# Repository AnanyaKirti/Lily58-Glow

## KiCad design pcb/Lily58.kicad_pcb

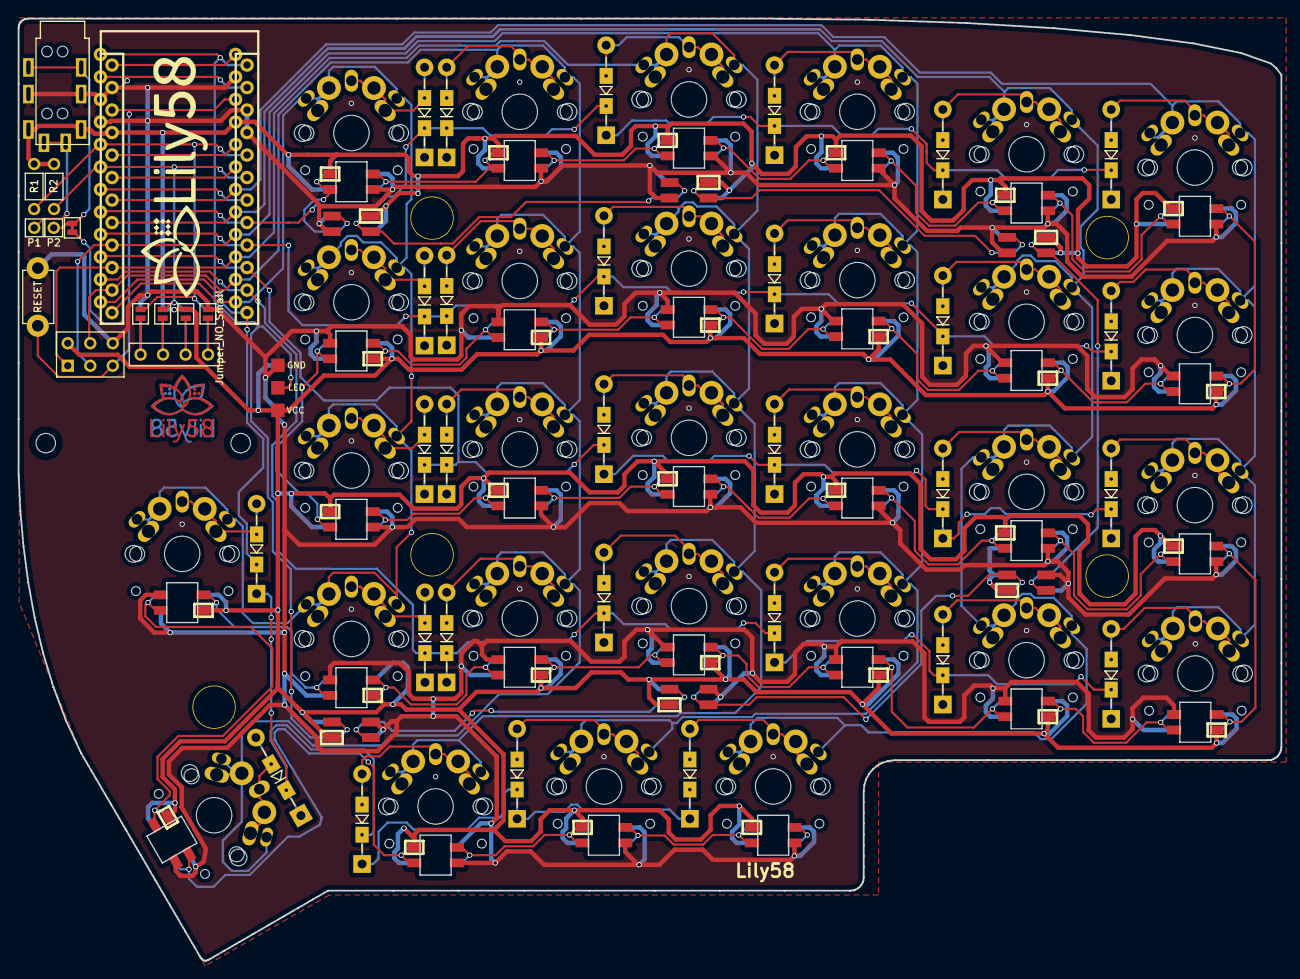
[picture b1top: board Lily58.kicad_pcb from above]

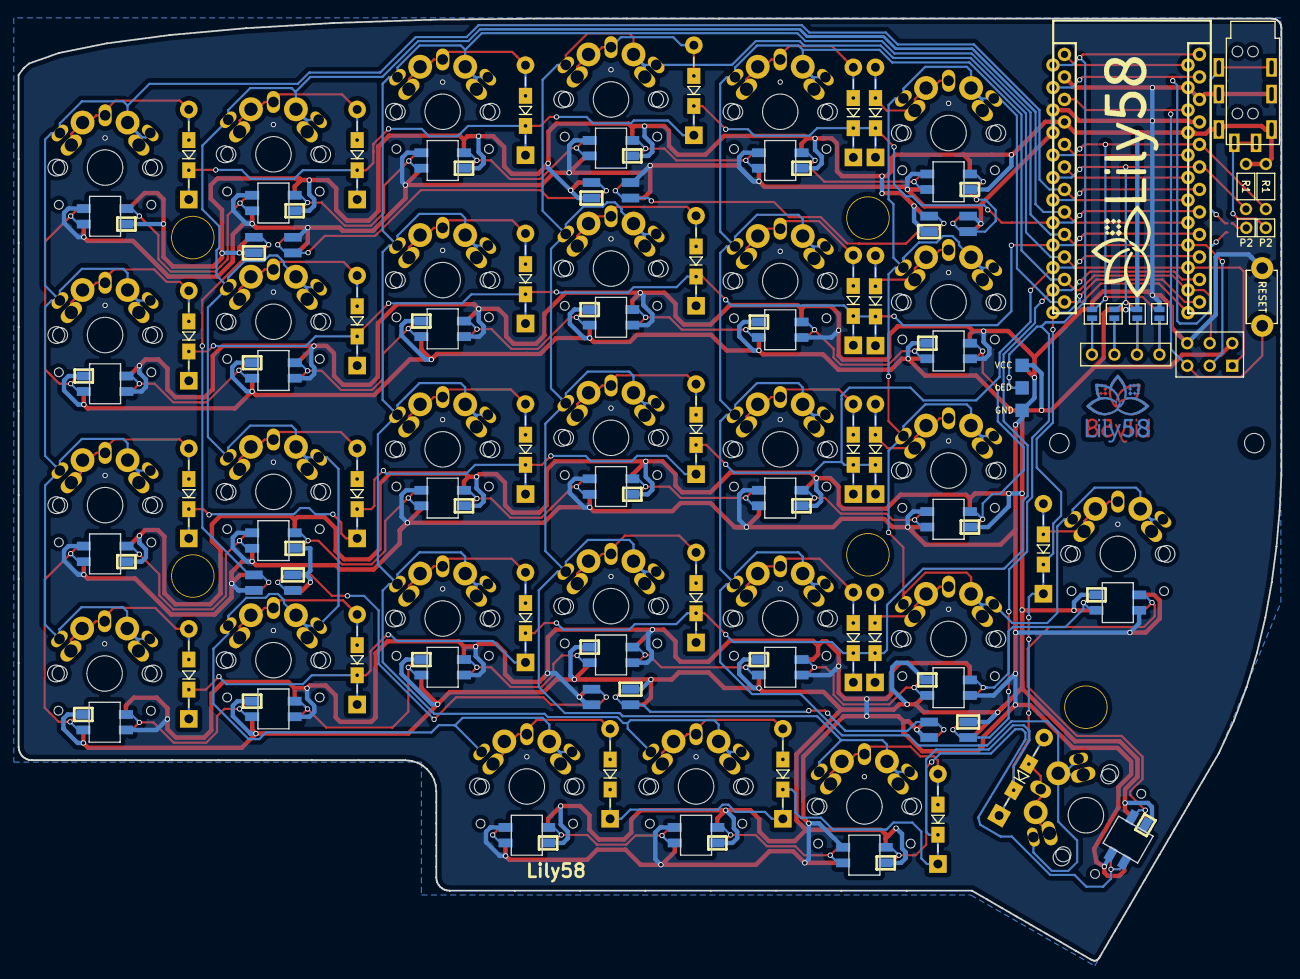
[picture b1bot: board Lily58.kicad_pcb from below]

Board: 2 copper layers, 142.5 x 106.3 mm, 119 parts (32 on the bottom side), 87 nets.

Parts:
D1, D2, D3, D4, D5, D6, D7, D8, D9, D10, D11, D12, D13, D14, D15, D16, D17, D18, D19, D20, D21, D22, D23, D24, D25, D26, D27, D28, D29: D; Diode_TH_SOD123
J1: LED; StripLED
J2: 4PIN; MJ-4PP-9
JP1, JP2, JP3, JP4, JP5, JP6, JP7, JP8: Jumper_NO_Small; Jumper
L1, L2, L3, L4, L5, L6, L7, L8, L9, L10, L11, L12, L13, L14, L15, L16, L17, L18, L19, L20, L21, L22, L23, L24, L25, L26, L27, L28, L29: SK6812mini; SK6812MINI_rev
L30, L31, L32, L33, L34, L35: SK6812mini; SK6812MINI_underglow_rev
P1, P2: i2c_pin; 1pin_conn
P3: ICSP
P4: OLED; MY_SIL-4
R1, R2: R; RESISTOR_mini
RSW1: SW_RST; TACT_SWITCH_TVBP06
SW1, SW2, SW3, SW4, SW5, SW6, SW7, SW8, SW9, SW10, SW11, SW12, SW13, SW14, SW15, SW16, SW17, SW18, SW19, SW20, SW21, SW22, SW23, SW24, SW25, SW27, SW28, SW29: SW_PUSH; MX_PG1350_FLIP_HOLES_18mm
SW26: SW_PUSH; MX_PG1350_FLIP_HOLES_27mm
TH1, TH2: HOLE; HOLE_M2
TH3, TH4, TH5, TH6, TH7: HOLE; HOLE_M2_TH
U1: ProMicro; ProMicro_rev2
W1: jumper; jumper_data

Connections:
DATA: U1.2, W1.1
GND: J1.3, J2.2, JP1.2, JP8.2, L1.2, L2.2, L3.2, L4.2, L5.2, L6.2, L7.2, L8.2, L9.2, L10.2, L11.2, L12.2, L13.2, L14.2, L15.2, L16.2, L17.2, L18.2, L19.2, L20.2, L21.2, L22.2, L23.2, L24.2, L25.2, L26.2, L27.2, L28.2, L29.2, L30.2, L31.2, L32.2, L33.2, L34.2, L35.2, P3.6, RSW1.1, U1.3, U1.4, U1.23
LED: J1.2, L33.3, U1.1
unnamed: D1.2, SW1.2
unnamed: D2.2, SW2.2
unnamed: D3.2, SW3.2
unnamed: D4.2, SW4.2
unnamed: D5.2, SW5.2
unnamed: D6.2, SW6.2
unnamed: D7.2, SW7.2
unnamed: D8.2, SW8.2
unnamed: D9.2, SW9.2
unnamed: D10.2, SW10.2
unnamed: D11.2, SW11.2
unnamed: D12.2, SW12.2
unnamed: D13.2, SW13.2
unnamed: D14.2, SW14.2
unnamed: D15.2, SW15.2
unnamed: D16.2, SW16.2
unnamed: D17.2, SW17.2
unnamed: D18.2, SW18.2
unnamed: D19.2, SW19.2
unnamed: D20.2, SW20.2
unnamed: D21.2, SW21.2
unnamed: D22.2, SW22.2
unnamed: D23.2, SW23.2
unnamed: D24.2, SW24.2
unnamed: D25.2, SW25.2
unnamed: D26.2, SW26.2
unnamed: D27.2, SW27.2
unnamed: D28.2, SW28.2
unnamed: D29.2, SW29.2
unnamed: J2.3, P2.1, W1.2
unnamed: J2.4, P1.1
unnamed: JP1.1, JP5.1, P4.4
unnamed: JP2.1, JP6.1, P4.3
unnamed: JP3.1, JP7.1, P4.2
unnamed: JP4.1, JP8.1, P4.1
unnamed: L1.1, L2.3
unnamed: L1.3, L30.1
unnamed: L2.1, L3.3
unnamed: L3.1, L4.3
unnamed: L4.1, L5.3
unnamed: L5.1, L6.3
unnamed: L7.3, L8.1
unnamed: L8.3, L9.1
unnamed: L9.3, L10.1
unnamed: L10.3, L11.1
unnamed: L11.3, L12.1
unnamed: L6.1, L12.3
unnamed: L13.1, L14.3
unnamed: L7.1, L13.3
unnamed: L14.1, L15.3
unnamed: L15.1, L16.3
unnamed: L16.1, L17.3
unnamed: L17.1, L18.3
unnamed: L18.1, L24.3
unnamed: L19.1, L25.3
unnamed: L19.3, L20.1
unnamed: L20.3, L21.1
unnamed: L21.3, L22.1
unnamed: L22.3, L23.1
unnamed: L23.3, L24.1
unnamed: L25.1, L26.3
unnamed: L26.1, L27.3
unnamed: L27.1, L28.3
unnamed: L28.1, L29.3
unnamed: L30.3, L31.1
unnamed: L31.3, L32.1
unnamed: L32.3, L35.1
unnamed: L33.1, L34.3
unnamed: L34.1, L35.3
RESET: P3.5, RSW1.2, U1.22
SCL: JP3.2, JP6.2, R2.2, U1.6
SDA: JP4.2, JP5.2, R1.2, U1.5
VCC: J1.1, J2.1, JP2.2, JP7.2, L1.4, L2.4, L3.4, L4.4, L5.4, L6.4, L7.4, L8.4, L9.4, L10.4, L11.4, L12.4, L13.4, L14.4, L15.4, L16.4, L17.4, L18.4, L19.4, L20.4, L21.4, L22.4, L23.4, L24.4, L25.4, L26.4, L27.4, L28.4, L29.4, L30.4, L31.4, L32.4, L33.4, L34.4, L35.4, P3.2, R1.1, R2.1, U1.21
col0: SW6.1, SW12.1, SW18.1, SW24.1, U1.18
col1: SW5.1, SW11.1, SW17.1, SW23.1, SW29.1, U1.17
col2: P3.3, SW4.1, SW10.1, SW16.1, SW22.1, SW28.1, U1.16
col3: P3.1, SW3.1, SW9.1, SW15.1, SW21.1, SW27.1, U1.15
col4: P3.4, SW2.1, SW8.1, SW14.1, SW20.1, SW26.1, U1.14
col5: SW1.1, SW7.1, SW13.1, SW19.1, SW25.1, U1.13
row0: D1.1, D2.1, D3.1, D4.1, D5.1, D6.1, U1.8
row1: D7.1, D8.1, D9.1, D10.1, D11.1, D12.1, U1.9
row2: D13.1, D14.1, D15.1, D16.1, D17.1, D18.1, U1.10
row3: D19.1, D20.1, D21.1, D22.1, D23.1, D24.1, U1.11
row4: D25.1, D26.1, D27.1, D28.1, D29.1, U1.12

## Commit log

2020-07-05 added name + case file
    added name
